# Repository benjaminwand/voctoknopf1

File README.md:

This is a hardware-interface vor [voctomix](https://github.com/voc/voctomix/tree/master/voctocore), developed late 2017 and tried in a few talks at 34c3.

### Key features are:

* Custom PCB
* Cherry MX switches with custom 3D-printed keycaps
* 3D-printed top and bottom enclosure parts “sandwiched” around the PCB
* Arduino Nano which sends commands to a computer via USB
* Computer relays the commands to the voctomix software via [socat](https://linux.die.net/man/1/socat)
* is supposed to learn to speak TPC on its own (was not implemented on 34c3)

This is a community project with help from many friends.

The **keycaps** are [gothic.FCStd](https://github.com/benjaminwand/Cherry-MX-keycaps/tree/master/with%20LED), 20 * 33,5 mm for the composite mode buttons and 25 * 25 mm for the camera/channel buttons and the take button. Please adjust the side lengths in the spreadsheet of the file, but there are also stl files in the ‘case’ folder.

### Lessons learnt after PCB production V 1.0: 
* slightly wrong footprint for resistors, too short
* wrong footprint for cherry switches, contacts for LEDs are too far apart
* the Cherry MX I got from reichelt.de aren’t for PCB mount, be more careful when shopping
* wrong footprint for StreamOn switch, fix: bend up two diagonal contacts
* 1.5k ohm pull-up-resistors are required between A4 and 5V and A5 and 5V
* the buttons would look more evenly illuminated if the LED was behind the switches -> turn the Cherry MX around 180°

See [here](graphics/bugfixes.jpg) for a photo with hardware fixes.

### Lessons learnt regarding the case
* I’ve actually included small changes into the file after printing, print as-is, and slice everything the way around it is supposed to end up. Yes, printing the buttons upside down would be faster but looks ugly. I found it easier to remove the support-material when the buttons were printed with raft.
* Print everything with transparent filament and then paint up the upper side of the case (except from the letters !!!) with a dark-ish pen that isn’t water-soluble. Due to the LEDs inside, the letters become illuminated.

### Shopping list
* 1 arduino nano (clone)
* 1 ethernet-shield for arduino nano
* 12 Cherry MX switches with holes for LEDs, for PCB mount. I used ‘clear’ and would go for ‘brown’ next time.
* 12 3mm LEDs, 4 red, 4 blue, 4 other color (yellow). alternatively there are probably special LEDs für Cherry MX but I didn’t have the time for searching
* 1 tact switch for StreamOn-button 
* 1 5mm LED red
* 1 5mm LED green
* 14 resistors 220
* 13 resistors 10k
* 2 resistors 1.5k
* 4 nuts and bolts M3 (best: screws with countersunk head)

### Status
One device has been built so far and has been successfully used in a few talks on the 34th Chaos Communication Congress.

### References
* [Cherry MX keycaps](https://github.com/benjaminwand/Cherry-MX-keycaps)
* [Geekend Prototype](https://github.com/benjaminwand/voctoknopf-Geekend-prototype)
* [Voctoknopf as a handheld controller](https://github.com/benjaminwand/voctoplay)

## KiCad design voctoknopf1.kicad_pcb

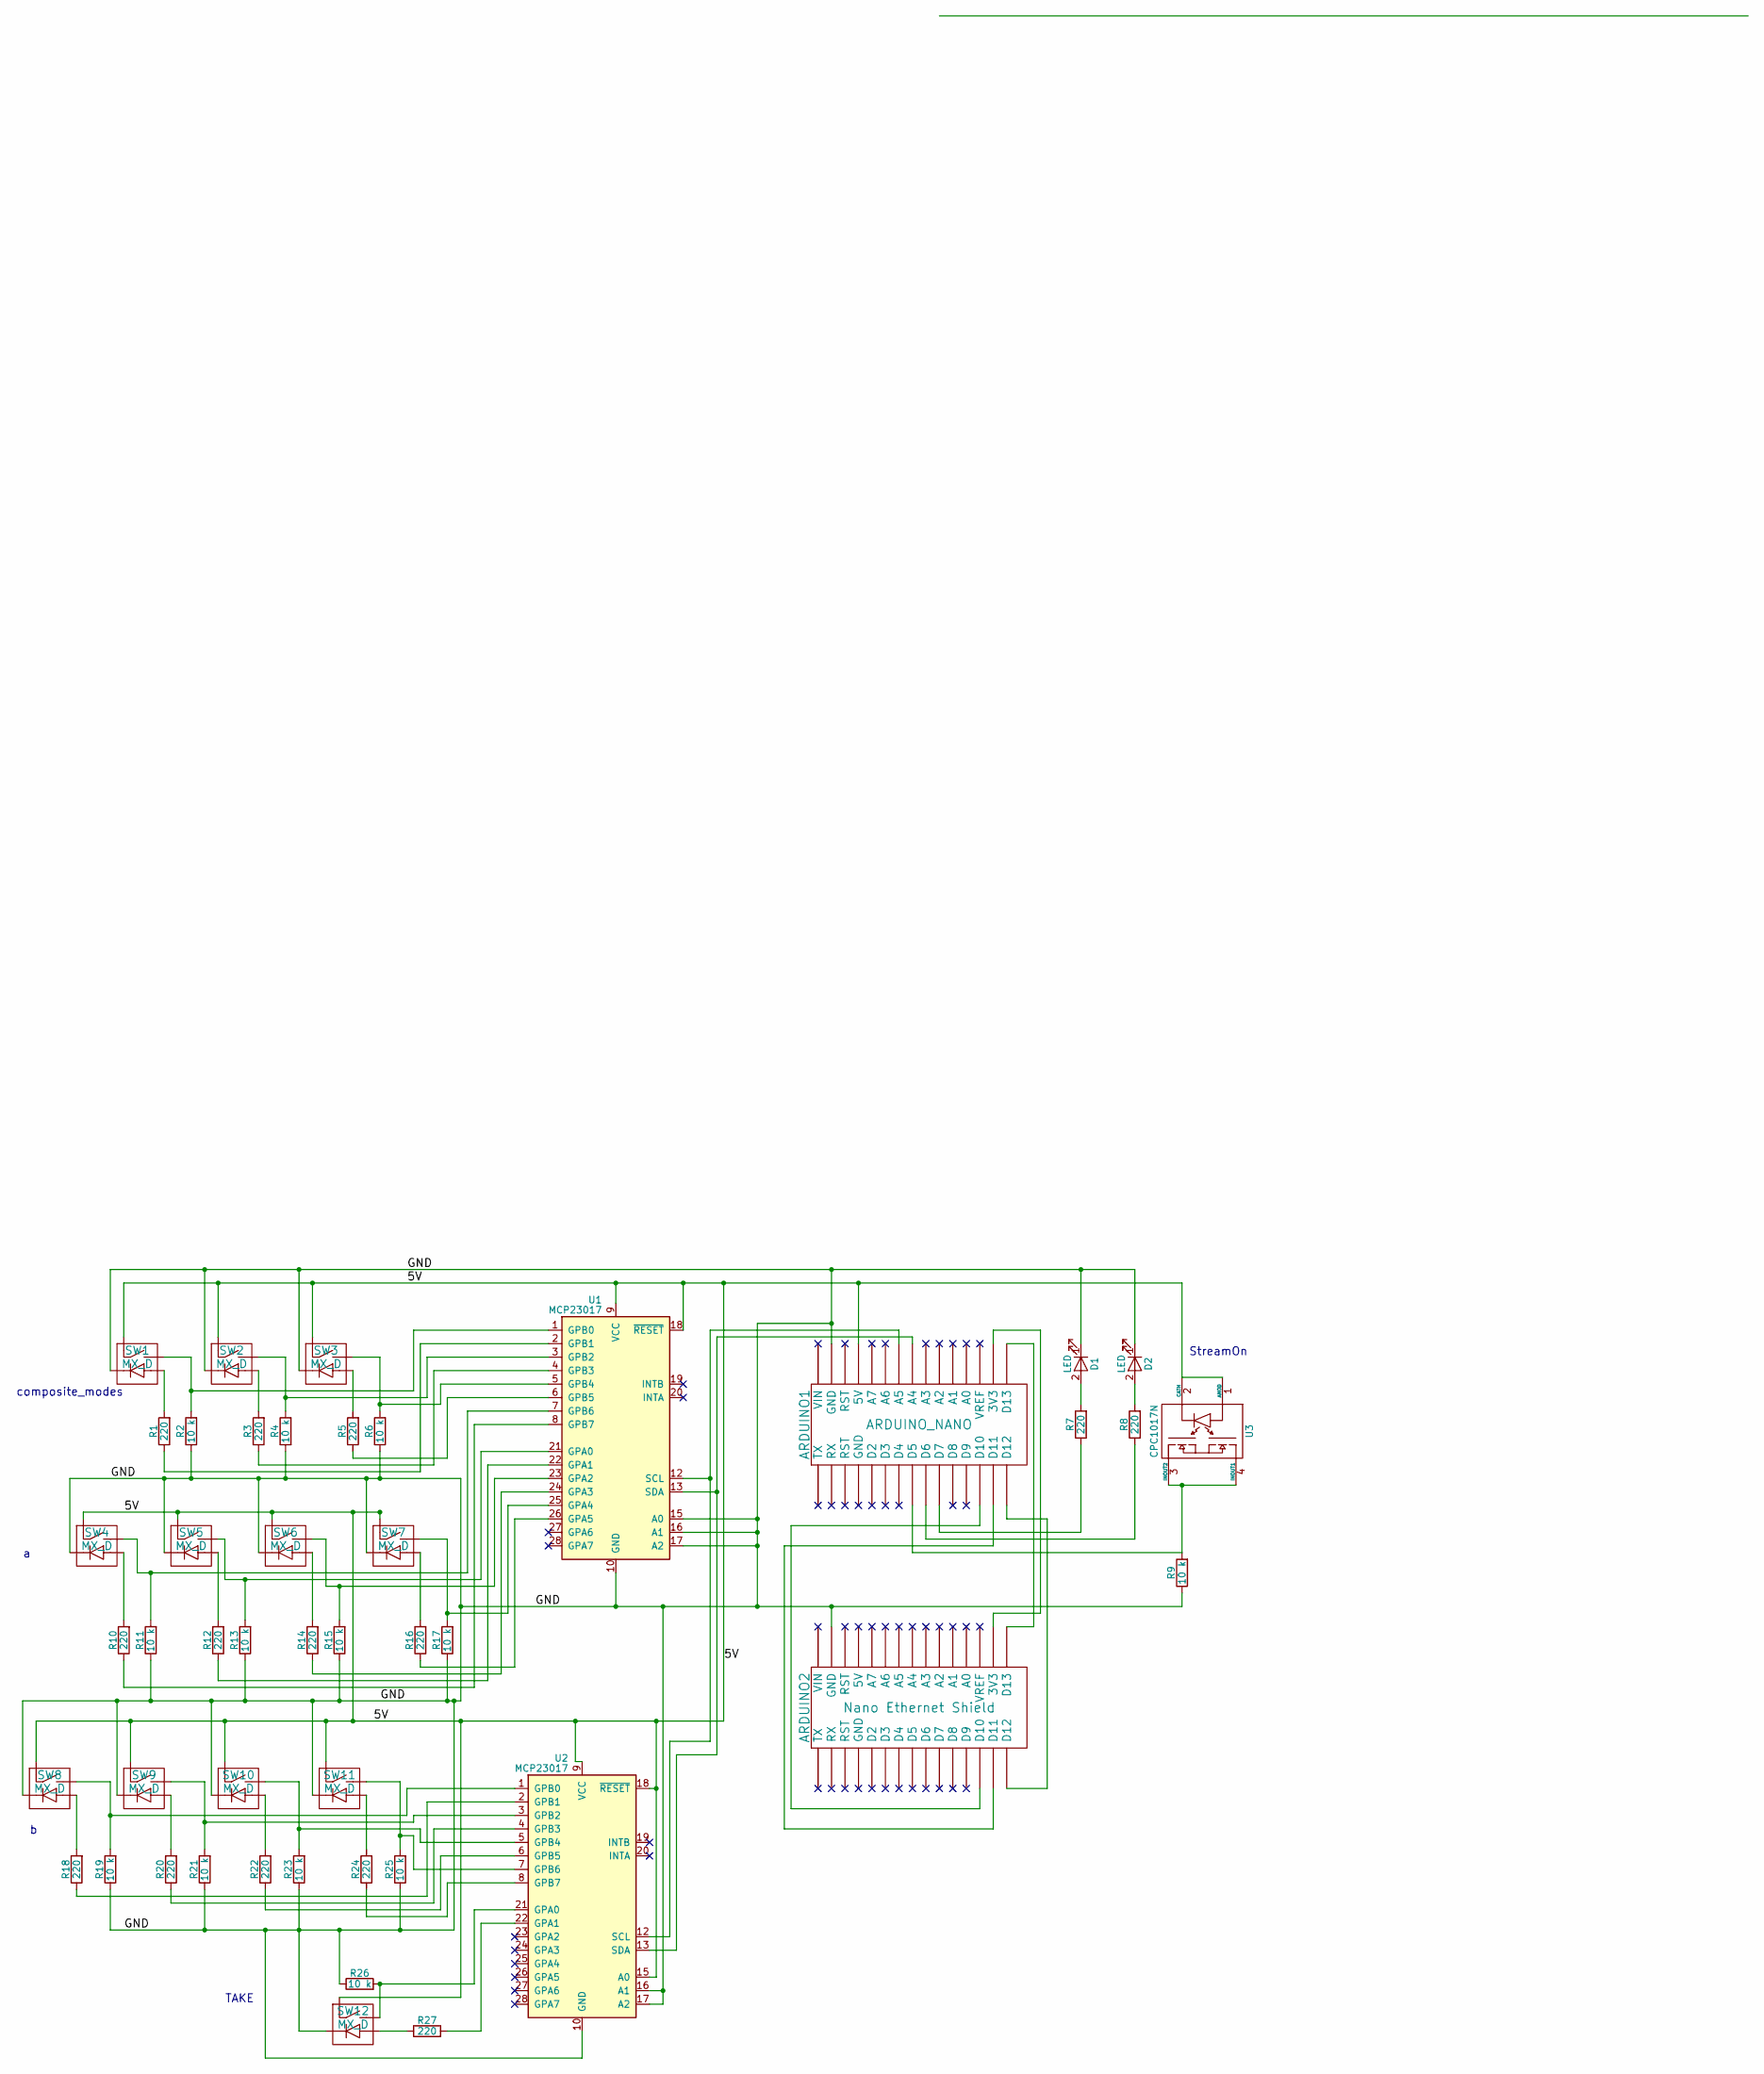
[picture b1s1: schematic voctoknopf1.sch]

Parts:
ARDUINO1: ARDUINO_NANO; Arduino_Nano_WithMountingHoles
ARDUINO2: Nano Ethernet Shield; Arduino_Nano_WithMountingHoles
D1, D2: LED; LED_D5.0mm
R1, R3, R5, R7, R8, R10, R12, R14, R16, R18, R20, R22, R24, R27: 220; R_Axial_DIN0207_L6.3mm_D2.5mm_P7.62mm_Horizontal
R2, R4, R6, R9, R11, R13, R15, R17, R19, R21, R23, R25, R26: 10 k; R_Axial_DIN0207_L6.3mm_D2.5mm_P7.62mm_Horizontal
SW1, SW2, SW3, SW4, SW5, SW6, SW7, SW8, SW9, SW10, SW11, SW12: MX_D; SW_PCB_4PIN
U1, U2: MCP23017; DIP-28_W7.62mm_LongPads
U3: CPC1017N; SW_DIP_x2_W8.61mm_Slide_LowProfile

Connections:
/5V: ARDUINO1.27 (5V), SW1.1 (A), SW2.1 (A), SW3.1 (A), SW4.1 (A), SW5.1 (A), SW6.1 (A), SW7.1 (A), SW8.1 (A), SW9.1 (A), SW10.1 (A), SW11.1 (A), SW12.1 (A), U1.9 (VCC), U1.18 (~RESET), U2.9 (VCC), U2.15 (A0), U2.18 (~RESET), U3.1 (ANOD), U3.2 (CATH)
/GND: ARDUINO1.29 (GND), ARDUINO2.29 (GND), D1.1 (K), D2.1 (K), R2.1, R4.1, R6.1, R9.1, R11.1, R13.1, R15.1, R17.1, R19.1, R21.1, R23.1, R25.1, R26.1, SW1.4 (D), SW2.4 (D), SW3.4 (D), SW4.4 (D), SW5.4 (D), SW6.4 (D), SW7.4 (D), SW8.4 (D), SW9.4 (D), SW10.4 (D), SW11.4 (D), SW12.4 (D), U1.10 (GND), U1.15 (A0), U1.16 (A1), U1.17 (A2), U2.10 (GND), U2.16 (A1), U2.17 (A2)
unnamed: ARDUINO1.8 (D5), R9.2, U3.3 (INOUT2), U3.4 (INOUT1)
unnamed: ARDUINO1.9 (D6), R8.1
unnamed: ARDUINO1.10 (D7), R7.1
unnamed: ARDUINO1.13 (D10), ARDUINO2.13 (D10)
unnamed: ARDUINO1.14 (D11), ARDUINO2.14 (D11)
unnamed: ARDUINO1.15 (D12), ARDUINO2.15 (D12)
unnamed: ARDUINO1.16 (D13), ARDUINO2.16 (D13)
unnamed: ARDUINO1.17 (3V3), ARDUINO2.17 (3V3)
unnamed: ARDUINO1.23 (A4), U1.13 (SDA), U2.13 (SDA)
unnamed: ARDUINO1.24 (A5), U1.12 (SCL), U2.12 (SCL)
unnamed: D1.2 (A), R7.2
unnamed: D2.2 (A), R8.2
unnamed: R1.1, U1.2 (GPB1)
unnamed: R1.2, SW1.3 (B)
unnamed: R2.2, SW1.2 (B), U1.1 (GPB0)
unnamed: R3.1, U1.4 (GPB3)
unnamed: R3.2, SW2.3 (B)
unnamed: R4.2, SW2.2 (B), U1.3 (GPB2)
unnamed: R5.1, U1.6 (GPB5)
unnamed: R5.2, SW3.3 (B)
unnamed: R6.2, SW3.2 (B), U1.5 (GPB4)
unnamed: R10.1, U1.8 (GPB7)
unnamed: R10.2, SW4.3 (B)
unnamed: R11.2, SW4.2 (B), U1.7 (GPB6)
unnamed: R12.1, U1.22 (GPA1)
unnamed: R12.2, SW5.3 (B)
unnamed: R13.2, SW5.2 (B), U1.21 (GPA0)
unnamed: R14.1, U1.24 (GPA3)
unnamed: R14.2, SW6.3 (B)
unnamed: R15.2, SW6.2 (B), U1.23 (GPA2)
unnamed: R16.1, U1.26 (GPA5)
unnamed: R16.2, SW7.3 (B)
unnamed: R17.2, SW7.2 (B), U1.25 (GPA4)
unnamed: R18.1, U2.2 (GPB1)
unnamed: R18.2, SW8.3 (B)
unnamed: R19.2, SW8.2 (B), U2.1 (GPB0)
unnamed: R20.1, U2.4 (GPB3)
unnamed: R20.2, SW9.3 (B)
unnamed: R21.2, SW9.2 (B), U2.3 (GPB2)
unnamed: R22.1, U2.6 (GPB5)
unnamed: R22.2, SW10.3 (B)
unnamed: R23.2, SW10.2 (B), U2.5 (GPB4)
unnamed: R24.1, U2.8 (GPB7)
unnamed: R24.2, SW11.3 (B)
unnamed: R25.2, SW11.2 (B), U2.7 (GPB6)
unnamed: R26.2, SW12.2 (B), U2.21 (GPA0)
unnamed: R27.1, SW12.3 (B)
unnamed: R27.2, U2.22 (GPA1)

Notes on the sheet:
StreamOn
composite_modes
TAKE

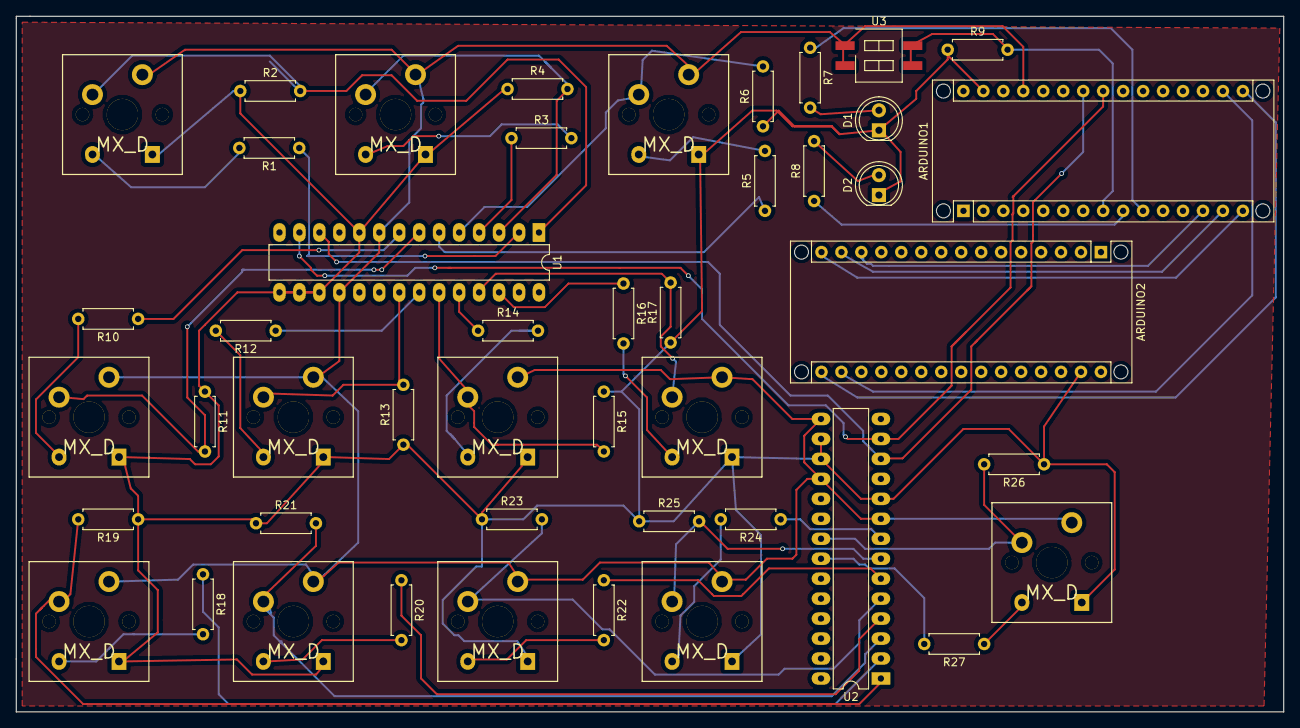
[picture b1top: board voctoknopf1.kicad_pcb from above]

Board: 2 copper layers, 161.2 x 88.5 mm, 46 parts (0 on the bottom side), 50 nets.

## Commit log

2017-11-23 initial commit
    hässlich aber wahr
2017-11-24 mock-up added
2017-11-29 29.11.
    erster Versuch mit ethernet shiled und ich habe einen arduino nano für kicad gefunden
2017-11-29 case 3d file, more pcb work
2017-11-29 pcb weiter machen
2017-11-29 more pcb foo
2017-11-29 more pcb
2017-11-29 PCB und Grafiken
2017-11-29 circuit
2017-11-30 last today
2017-11-30 netlist
2017-11-30 scematic + netlist
2017-11-30 sorting components on pcb
2017-11-30 pcb work
2017-11-30 pbc work
2017-11-30 last saved November 2017
2017-12-02 ethernet shild the right way around
2017-12-02 irgendwas mit footprints, und gerberfiles
2017-12-03 dpi 89
2017-12-03 ordentliche Proportionen
2017-12-03 pbc done
2017-12-03 pcb bug free (so it says), and new freecad file
2017-12-04 aufräumen, gerber files for manufacturer
2017-12-04 minor edit
2017-12-05 removed superfluous via
2017-12-06 readme
2017-12-14 readme-update, new software file (wire)
2017-12-14 code
2017-12-18 order
2017-12-18 case design
2017-12-18 case
2017-12-19 more lessons learnt + case work
2017-12-19 software steruktur aufräumen
2017-12-19 case work
2017-12-19 more lessons learnt
2017-12-20 shopping list
2017-12-20 software
2017-12-20 ordentlichere io-port-expander belegung
2017-12-21 software aufräumen
2017-12-21 aktueller look
2017-12-21 shiny at start
2017-12-25 LED test when booting
2017-12-26 take buton leuchtet jetzt auch im setup
2017-12-28 geht jetzt
2017-12-28 live is string?
2017-12-28 1 mal pro sekunde fragen
2017-12-28 < oder > ? ...
2017-12-28 hat funktioniert dank gruetzkopf
2017-12-29 voctocore pushed von selber
2017-12-30 wie heißt das Device auf meinem Rechner?
2017-12-31 formating
2017-12-31 legacy software sortieren
2018-01-01 add platformio config files
2018-01-01 remove unnecessary white space
2018-01-01 fix indendation
2018-01-01 improve parantheses placement
2018-01-07 lessons learnt - case
2018-01-11 photo
2018-01-23 new readme
2018-01-23 practicing github
2018-01-23 gng einbinden
2018-01-23 more pretty
2018-03-30 implemented real-time readout of button states, refactored serial communication
2018-04-29 multi material front (optional)
